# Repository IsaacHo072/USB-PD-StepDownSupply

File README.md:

# USB-PD-StepDownSupply
A USB PD (Sink) DC-DC step-down power supply, requests 15-9V from PD source, provides 5V and 3.3V output.

## Components
Uses a FUSB302 and a STM32F030F4P6 for USB PD.
Two TPS62130 for step down.

## Program
A compiled firmware is provided for getting 15-9V from PD source. 
ST-Link, or any SWD programmer could be used for programming. 
Connect the ST-Link connector to CN1002 to download the firmware.

The firmware was modified from [manuelbl/zy12pdn-oss](https://github.com/manuelbl/zy12pdn-oss).

## Issues
This cannot be used with regular USB power supply (non-PD), or USB PD supply with 5V only power output, as TPS62130 cannot output 5V from 5V input. 

To be fixed:
- C1003 have wrong footprint size, 1206 should be used as a 0603 22uF capacitor voltage rating is too low.
- D1002 is bidirectional TVS diode, but if a unidirectional TVS diode is used, the polarity marking is on the wrong side. 
- Some trace could be bigger.

## Cost
The whole board could be made at around a few dollars.

When making 10 boards, each cost:
- FUSB302: $0.7
- STM32F030F4P6: $0.5
- TPS62130: $1*2
- HRO TYPE-C-31-M-12: $0.1
- Other components: $2 at most
- PCB: ~$10 (for 10)

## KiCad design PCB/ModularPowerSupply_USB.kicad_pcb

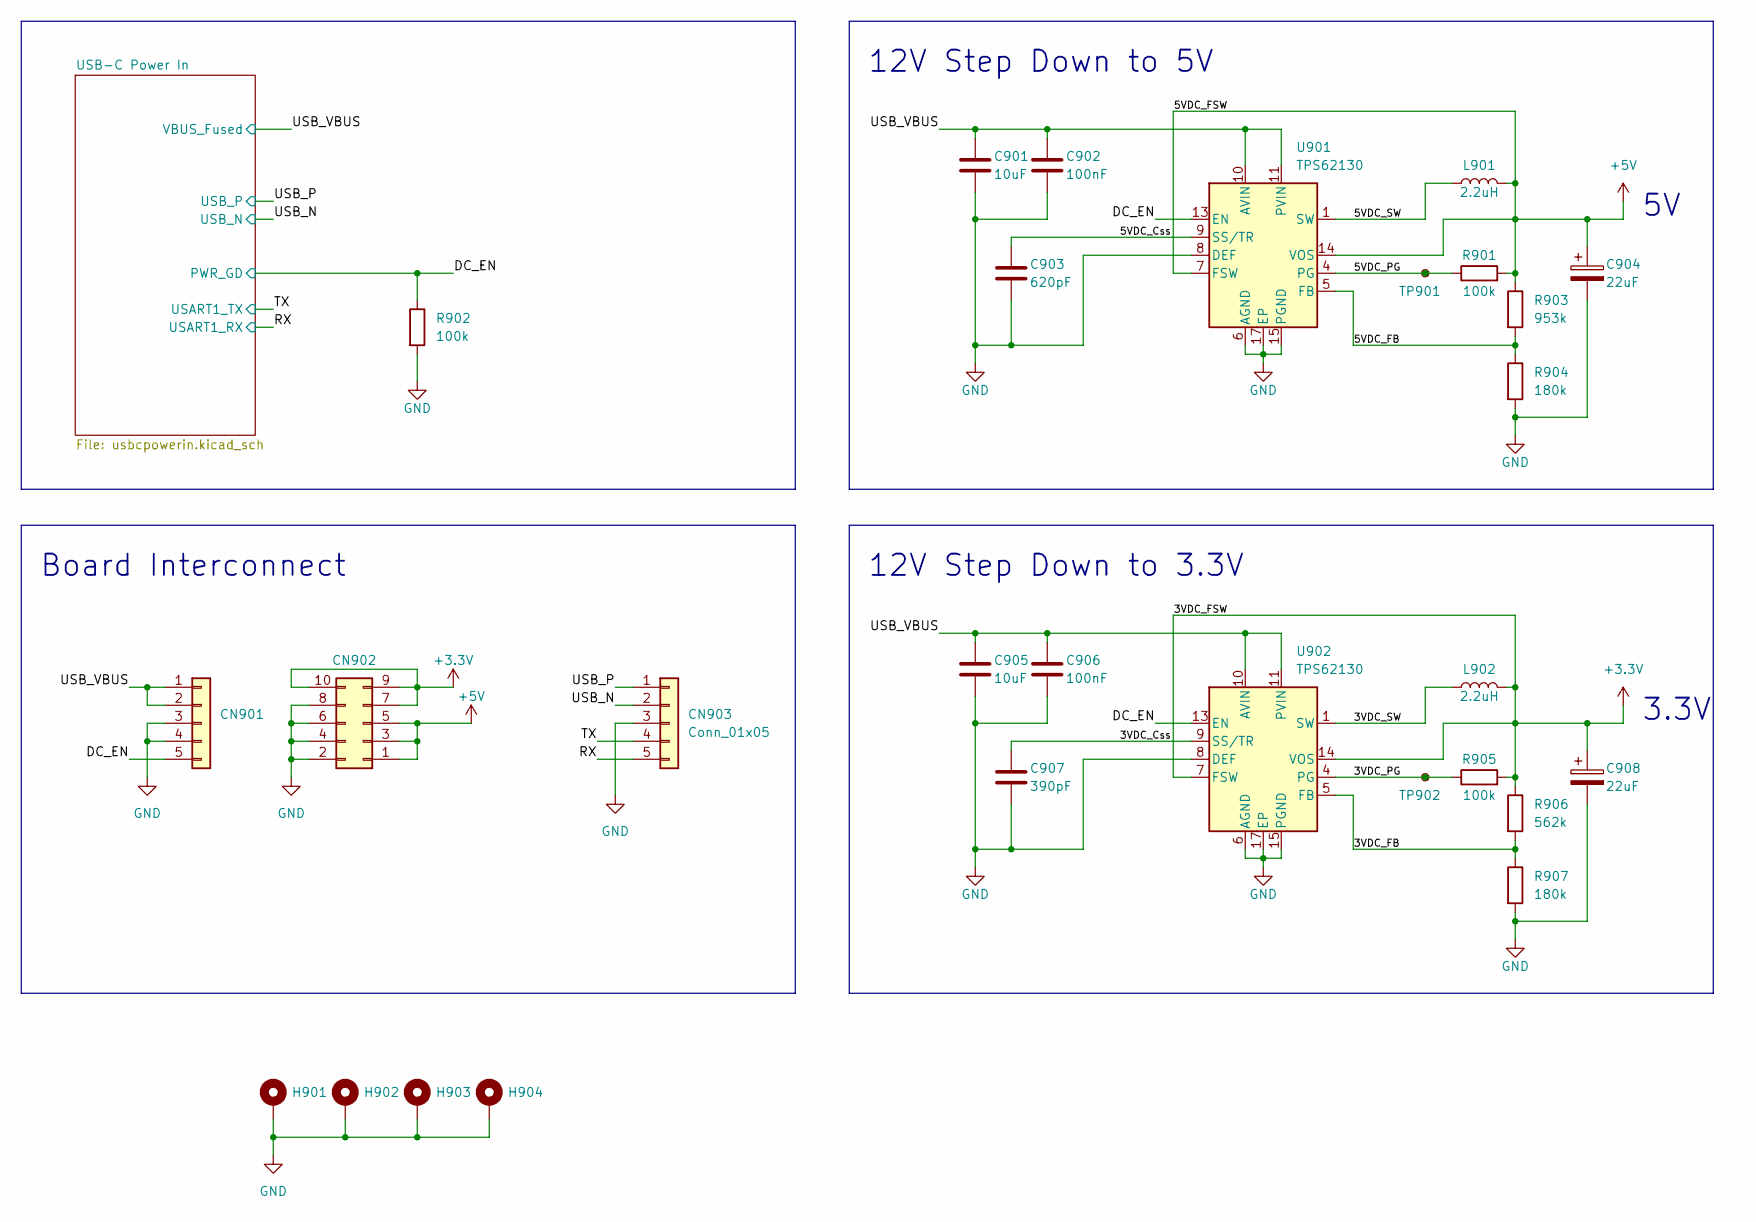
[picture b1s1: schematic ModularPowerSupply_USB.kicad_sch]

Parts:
C901, C905: 10uF; C_0603_1608Metric
C902, C906: 100nF; C_0603_1608Metric
C903: 620pF; C_0603_1608Metric
C904, C908: 22uF; CP_Elec_6.3x5.9
C907: 390pF; C_0603_1608Metric
CN901, CN903: Conn_01x05; PinHeader_1x05_P2.54mm_Vertical
CN902: Conn_02x05_Odd_Even; PinHeader_2x05_P2.54mm_Vertical
H901, H902, H903, H904: MountingHole_Pad; MountingHole_2.2mm_M2_Pad_Via
L901, L902: 2.2uH; Panasonic Inductor KVP
R901, R902, R905: 100k; R_0603_1608Metric
R903: 953k; R_0603_1608Metric
R904, R907: 180k; R_0603_1608Metric
R906: 562k; R_0603_1608Metric
TP901, TP902: TestPoint_Small; TestPoint_Pad_D1.0mm
U901, U902: TPS62130; VQFN-16-1EP_3x3mm_P0.5mm_EP1.68x1.68mm_ThermalVias

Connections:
+3.3V: C908.1, CN902.7, CN902.9, CN902.10, L902.2, R905.2, R906.1, U902.7 (FSW), U902.14 (VOS)
+5V: C904.1, CN902.1, CN902.3, CN902.5, L901.2, R901.2, R903.1, U901.7 (FSW), U901.14 (VOS)
/3VDC_Css: C907.1, U902.9 (SS/TR)
/3VDC_FB: R906.2, R907.1, U902.5 (FB)
/3VDC_PG: R905.1, TP902.1, U902.4 (PG)
/3VDC_SW: L902.1, U902.1 (SW), U902.2 (SW), U902.3 (SW)
/5VDC_Css: C903.1, U901.9 (SS/TR)
/5VDC_FB: R903.2, R904.1, U901.5 (FB)
/5VDC_PG: R901.1, TP901.1, U901.4 (PG)
/5VDC_SW: L901.1, U901.1 (SW), U901.2 (SW), U901.3 (SW)
/DC_EN: CN901.5, R902.1, U901.13 (EN), U902.13 (EN); also elsewhere on the board
/RX: CN903.5; also elsewhere on the board
/TX: CN903.4; also elsewhere on the board
/USB_N: CN903.2; also elsewhere on the board
/USB_P: CN903.1; also elsewhere on the board
/USB_VBUS: C901.1, C902.1, C905.1, C906.1, CN901.1, CN901.2, U901.10 (AVIN), U901.11 (PVIN), U901.12 (PVIN), U902.10 (AVIN), U902.11 (PVIN), U902.12 (PVIN); also elsewhere on the board
GND: C901.2, C902.2, C903.2, C904.2, C905.2, C906.2, C907.2, C908.2, CN901.3, CN901.4, CN902.2, CN902.4, CN902.6, CN902.8, CN903.3, H901.1, H902.1, H903.1, H904.1, R902.2, R904.2, R907.2, U901.6 (AGND), U901.8 (DEF), U901.15 (PGND), U901.16 (PGND), U901.17 (EP), U902.6 (AGND), U902.8 (DEF), U902.15 (PGND), U902.16 (PGND), U902.17 (EP); also elsewhere on the board

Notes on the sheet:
3.3V
12V Step Down to 5V
12V Step Down to 3.3V
Board Interconnect

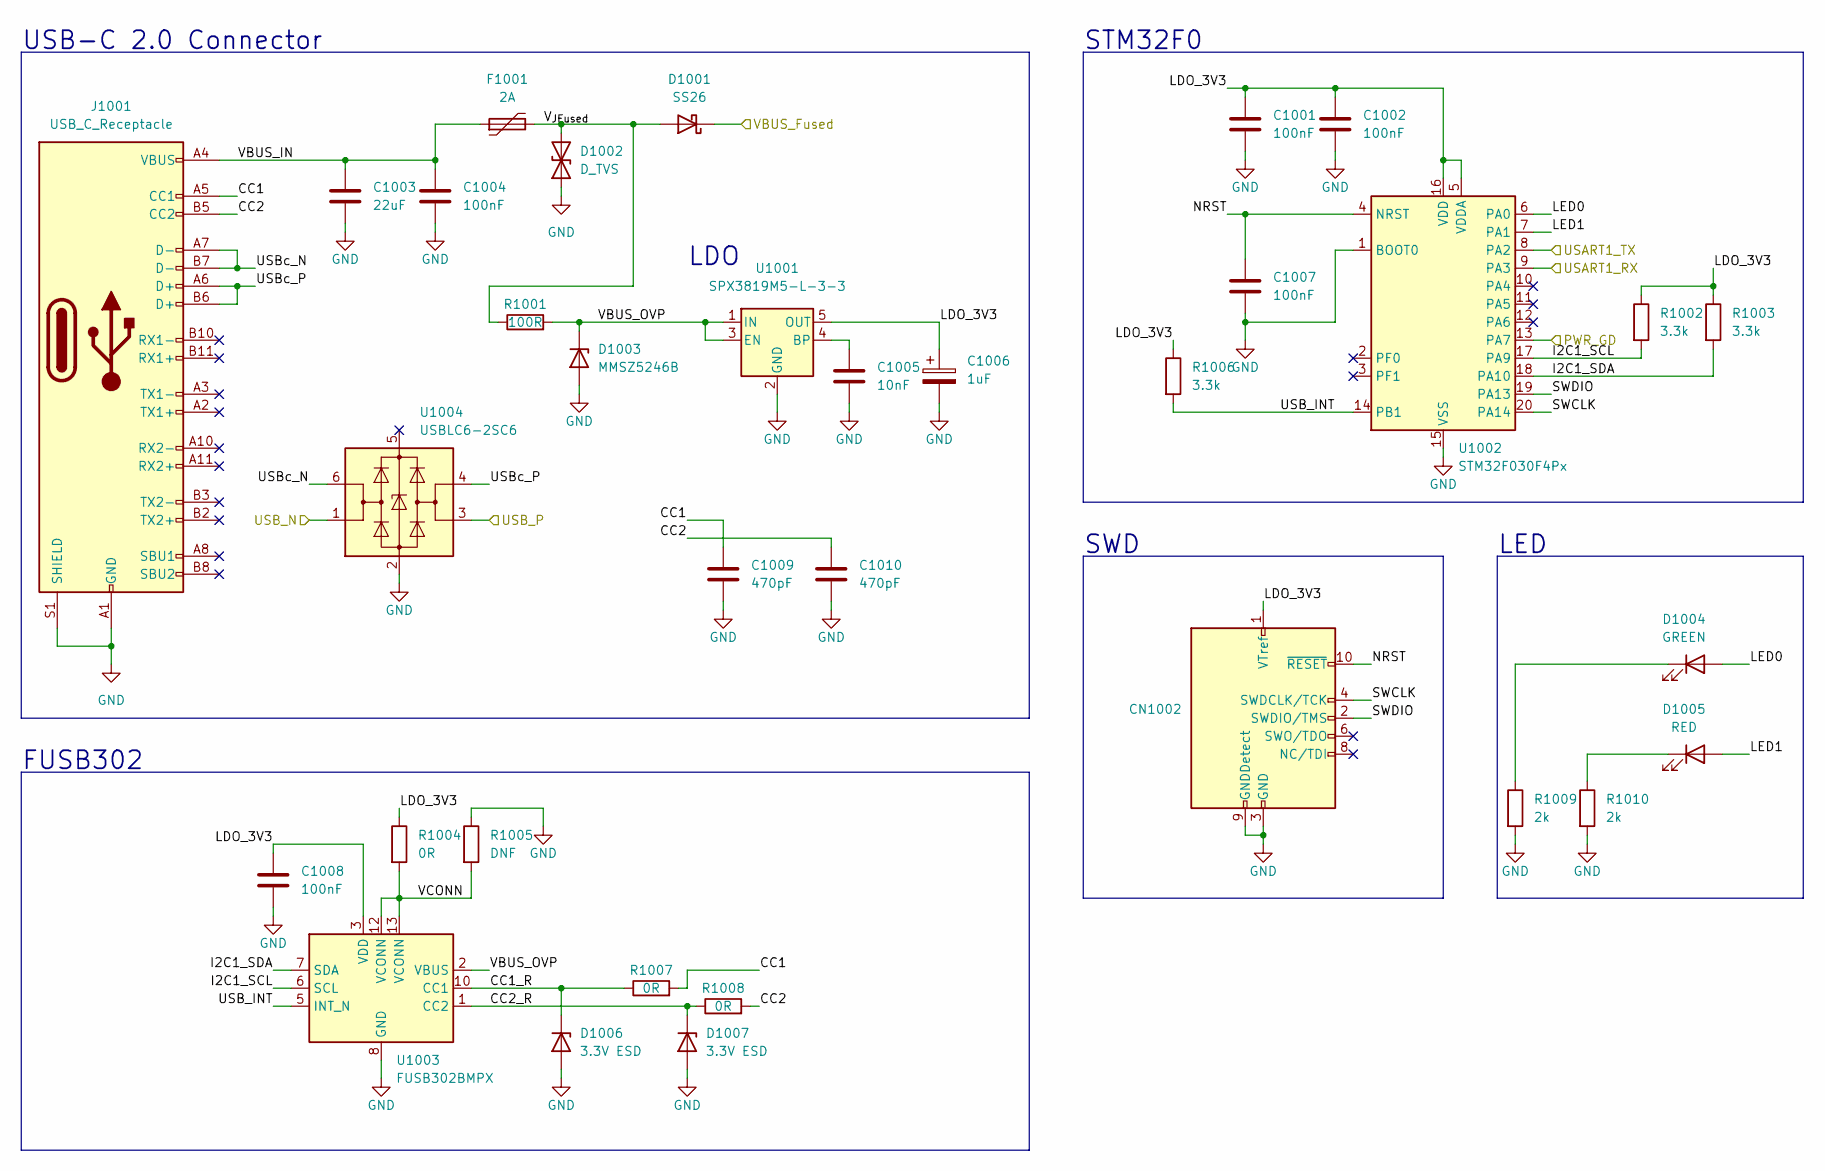
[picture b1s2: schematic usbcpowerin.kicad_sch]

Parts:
C1001, C1002, C1004, C1007, C1008: 100nF; C_0603_1608Metric
C1003: 22uF; C_0603_1608Metric
C1005: 10nF; C_0603_1608Metric
C1006: 1uF; CP_EIA-3216-18_Kemet-A
C1009, C1010: 470pF; C_0603_1608Metric
CN1002: Conn_ARM_JTAG_SWD_10; PinHeader_2x05_P1.27mm_Vertical
D1001: SS26; D_SMA
D1002: D_TVS; D_SMA
D1003: MMSZ5246B; D_SOD-123
D1004: GREEN; D_0603_1608Metric
D1005: RED; D_0603_1608Metric
D1006, D1007: 3.3V ESD; D_SOD-323
F1001: 2A; Fuse_1812_4532Metric
J1001: USB_C_Receptacle; USB_C_Receptacle_HRO_TYPE-C-31-M-12
R1001: 100R; R_0805_2012Metric
R1002, R1003, R1006: 3.3k; R_0603_1608Metric
R1004, R1007, R1008: 0R; R_0603_1608Metric
R1005: DNF; R_0603_1608Metric
R1009, R1010: 2k; R_0603_1608Metric
U1001: SPX3819M5-L-3-3; SOT-23-5
U1002: STM32F030F4Px; TSSOP-20_4.4x6.5mm_P0.65mm
U1003: FUSB302BMPX; WQFN-14-1EP_2.5x2.5mm_P0.5mm_EP1.45x1.45mm
U1004: USBLC6-2SC6; SOT-23-6

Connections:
/DC_EN: U1002.13 (PA7); also elsewhere on the board
/RX: U1002.9 (PA3); also elsewhere on the board
/TX: U1002.8 (PA2); also elsewhere on the board
/USB-C Power In/CC1: C1009.1, J1001.A5 (CC1), R1007.2
/USB-C Power In/CC1_R: D1006.1 (K), R1007.1, U1003.10 (CC1), U1003.11 (CC1)
/USB-C Power In/CC2: C1010.1, J1001.B5 (CC2), R1008.2
/USB-C Power In/CC2_R: D1007.1 (K), R1008.1, U1003.1 (CC2), U1003.14 (CC2)
/USB-C Power In/I2C1_SCL: R1002.2, U1002.17 (PA9), U1003.6 (SCL)
/USB-C Power In/I2C1_SDA: R1003.2, U1002.18 (PA10), U1003.7 (SDA)
/USB-C Power In/LDO_3V3: C1001.1, C1002.1, C1006.1, C1008.1, CN1002.1 (VTref), R1002.1, R1003.1, R1004.1, R1006.1, U1001.5 (OUT), U1002.5 (VDDA), U1002.16 (VDD), U1003.3 (VDD), U1003.4 (VDD)
/USB-C Power In/LED0: D1004.2 (A), U1002.6 (PA0)
/USB-C Power In/LED1: D1005.2 (A), U1002.7 (PA1)
/USB-C Power In/NRST: C1007.1, CN1002.10 (~RESET), U1002.4 (NRST)
/USB-C Power In/SWCLK: CN1002.4 (SWDCLK/TCK), U1002.20 (PA14)
/USB-C Power In/SWDIO: CN1002.2 (SWDIO/TMS), U1002.19 (PA13)
/USB-C Power In/USB_INT: R1006.2, U1002.14 (PB1), U1003.5 (INT_N)
/USB-C Power In/USBc_N: J1001.A7 (D-), J1001.B7 (D-), U1004.6 (I/O1)
/USB-C Power In/USBc_P: J1001.A6 (D+), J1001.B6 (D+), U1004.4 (I/O2)
/USB-C Power In/VBUS_IN: C1003.1, C1004.1, F1001.1, J1001.A4 (VBUS), J1001.A9 (VBUS), J1001.B4 (VBUS), J1001.B9 (VBUS)
/USB-C Power In/VBUS_OVP: D1003.1 (K), R1001.2, U1001.1 (IN), U1001.3 (EN), U1003.2 (VBUS)
/USB-C Power In/VCONN: R1004.2, R1005.2, U1003.12 (VCONN), U1003.13 (VCONN)
/USB-C Power In/V_{JFused}: D1001.2 (A), D1002.2 (A2), F1001.2, R1001.1
/USB_N: U1004.1 (I/O1); also elsewhere on the board
/USB_P: U1004.3 (I/O2); also elsewhere on the board
/USB_VBUS: D1001.1 (K); also elsewhere on the board
GND: C1001.2, C1002.2, C1003.2, C1004.2, C1005.2, C1006.2, C1007.2, C1008.2, C1009.2, C1010.2, CN1002.3 (GND), CN1002.5 (GND), CN1002.9 (GNDDetect), D1002.1 (A1), D1003.2 (A), D1006.2 (A), D1007.2 (A), J1001.A1 (GND), J1001.A12 (GND), J1001.B1 (GND), J1001.B12 (GND), J1001.S1 (SHIELD), R1005.1, R1009.2, R1010.2, U1001.2 (GND), U1002.1 (BOOT0), U1002.15 (VSS), U1003.8 (GND), U1003.9 (GND), U1003.15 (GND), U1004.2 (GND); also elsewhere on the board
unnamed: C1005.1, U1001.4 (BP)
unnamed: D1004.1 (K), R1009.1
unnamed: D1005.1 (K), R1010.1

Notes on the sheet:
STM32F0
FUSB302
LDO
LED
SWD
USB-C 2.0 Connector

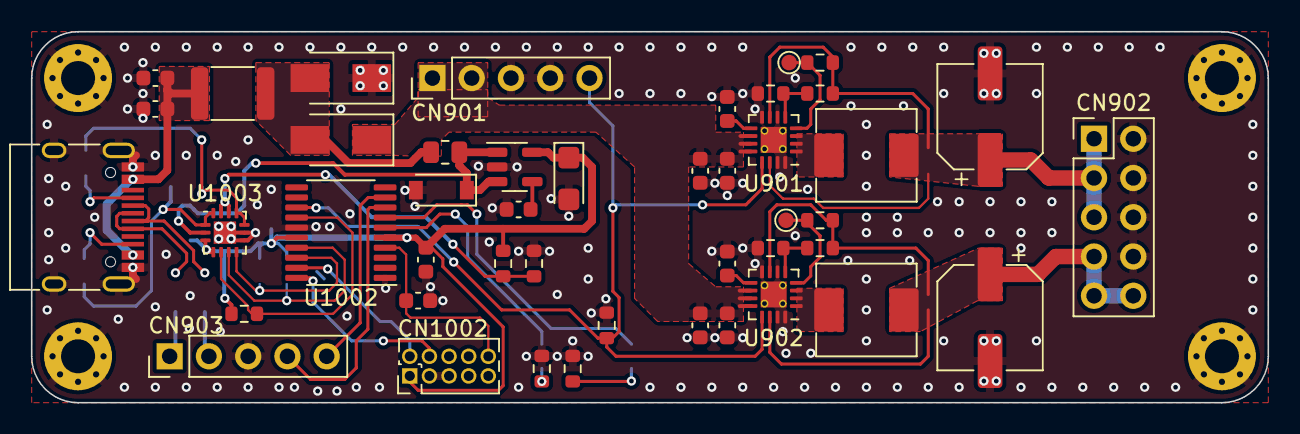
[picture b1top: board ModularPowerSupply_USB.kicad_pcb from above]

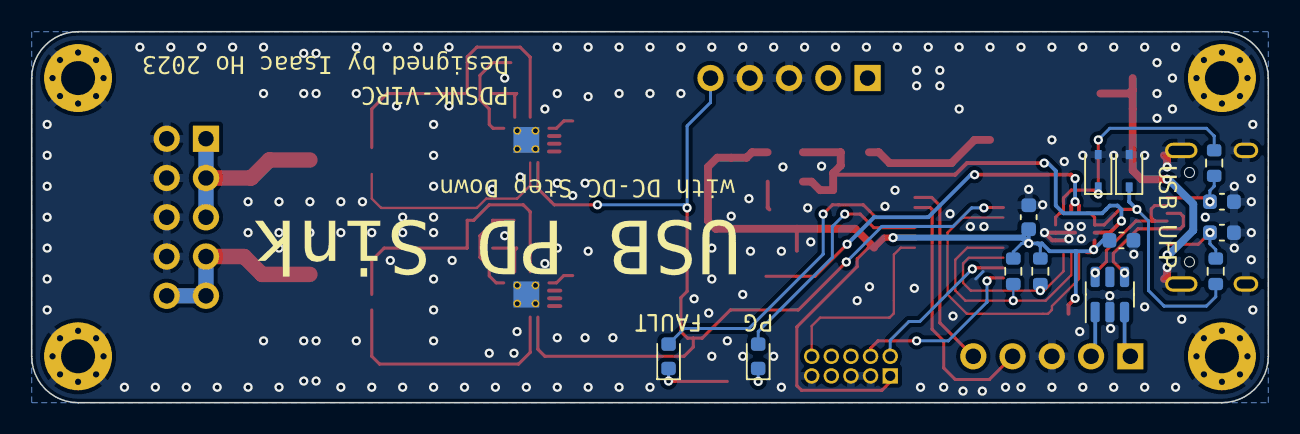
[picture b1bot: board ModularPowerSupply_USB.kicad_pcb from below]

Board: 2 copper layers, 80.0 x 24.0 mm, 66 parts (17 on the bottom side), 39 nets.

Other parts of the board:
kibuzzard-63BACD81: G***; kibuzzard-63BACD81
kibuzzard-63BACDB6: G***; kibuzzard-63BACDB6
kibuzzard-63BACE7D: G***; kibuzzard-63BACE7D
kibuzzard-63BACF17: G***; kibuzzard-63BACF17

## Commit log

2023-02-11 Initial Release
2023-02-11 Update README.md
    fixed typos
2023-02-11 Modified schematic
    changed C1003 size to 1206
    flipped D1002 around
2023-02-13 Create firmware (Request up to 15V).elf
    This firmware request up to 15V from the power source, if 15V is not available then it request 12V, then 9V, vice versa.
2023-02-16 updated firmware
